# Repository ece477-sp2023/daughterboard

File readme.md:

# Things to change for v3

-   mosfet rotation
-   bulk capacitor on 2.5V plane
-   bulk capacitors directly on all regulator outputs
-   ftdi analog power from 5V
-   1.1V slow start from 3vi, not 3v3

# want to have

-   crystal for fpga?
-   crystal for ftdi?
    -   only if needed
-   indicator LEDs?
    -   power
    -   usb

# make sure before starting v3

-   ftdi chip works
    -   if not, have easy way to program flash

# notes for v3

-   8 layer board might give more space on top
-   don't need 1v1 slow start connected to both 3v3 and 2v5, just use 3v3
-   look at regulator stock for 5->3, don't know if footprint chosen is common / available

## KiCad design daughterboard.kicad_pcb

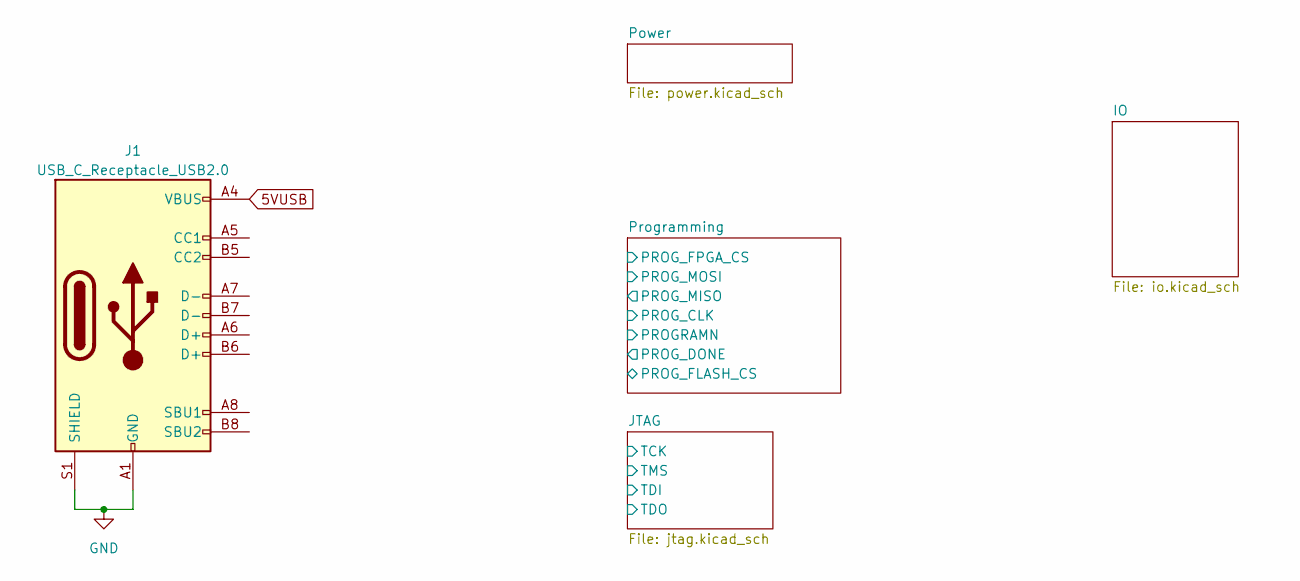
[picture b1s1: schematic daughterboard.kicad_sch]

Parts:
J1: USB_C_Receptacle_USB2.0; USB_C_GCT4105

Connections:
5VUSB: J1.A4 (VBUS), J1.A9 (VBUS), J1.B4 (VBUS), J1.B9 (VBUS); also elsewhere on the board
/JTAG/D+: J1.A6 (D+); also elsewhere on the board
/JTAG/D-: J1.A7 (D-); also elsewhere on the board
GND: J1.A1 (GND), J1.A12 (GND), J1.B1 (GND), J1.B12 (GND), J1.S1 (SHIELD); also elsewhere on the board

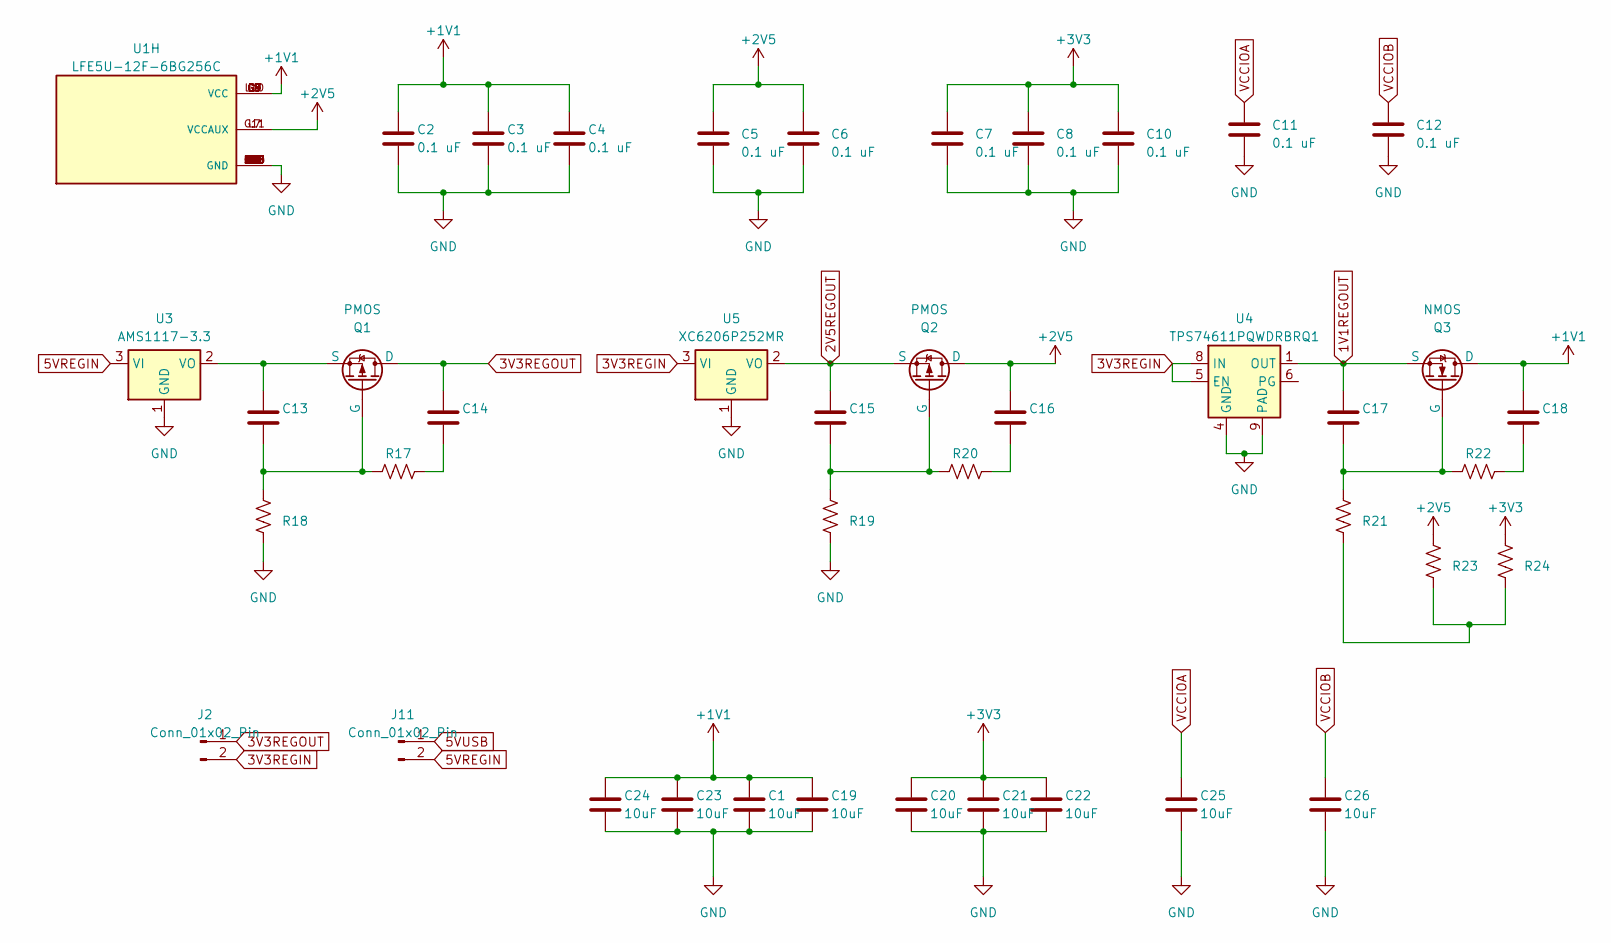
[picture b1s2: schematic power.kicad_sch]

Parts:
C1, C19, C20, C21, C22, C23, C24, C25, C26: 10uF; C_0805_2012Metric
C2, C3, C4, C5, C6, C7, C8, C10, C11, C12: 0.1 uF; C_0402_1005Metric
C13, C14, C15, C16, C17, C18: C_0805_2012Metric
J2, J11: Conn_01x02_Pin; PinHeader_1x02_P2.54mm_Vertical
Q1, Q2: PMOS; SOT-23-3
Q3: NMOS; SOT-23-3
R17, R18, R19, R20, R21, R22, R23, R24: R_0805_2012Metric
U1: LFE5U-12F-6BG256C; BGA256C80P16X16_1400X1400X170; PARTREV 2.0
U3: AMS1117-3.3; SOT-89-3
U4: TPS74611PQWDRBRQ1; Texas_S-PVSON-N8
U5: XC6206P252MR; SOT-23-3

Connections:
1V1REGOUT: C17.1, Q3.3 (S), U4.1 (OUT)
2V5REGOUT: C15.1, Q2.3 (S), U5.2 (VO)
3V3REGIN: J2.2, U4.5 (EN), U4.8 (IN), U5.3 (VI); also elsewhere on the board
3V3REGOUT: C14.1, J2.1, Q1.1 (D); also elsewhere on the board
5VREGIN: J11.2, U3.3 (VI); also elsewhere on the board
5VUSB: J11.1; also elsewhere on the board
+2V5: C5.1, C6.1, C16.1, Q2.1 (D), R23.2, U1.G11 (VCCAUX), U1.L7 (VCCAUX); also elsewhere on the board
GND: C1.2, C2.2, C3.2, C4.2, C5.2, C6.2, C7.2, C8.2, C10.2, C11.2, C12.2, C19.2, C20.2, C21.2, C22.2, C23.2, C24.2, C25.2, C26.2, R18.1, R19.1, U1.A1 (GND), U1.A16 (GND), U1.D2 (GND), U1.D15 (GND), U1.F8 (GND), U1.F9 (GND), U1.G8 (GND), U1.G10 (GND), U1.H1 (GND), U1.H8 (GND), U1.H9 (GND), U1.H10 (GND), U1.H16 (GND), U1.J8 (GND), U1.J9 (GND), U1.J10 (GND), U1.K6 (GND), U1.K7 (GND), U1.K8 (GND), U1.K9 (GND), U1.K10 (GND), U1.N2 (GND), U1.N15 (GND), U1.T1 (GND), U1.T5 (GND), U1.T12 (GND), U1.T16 (GND), U3.1 (GND), U4.4 (GND), U4.9 (PAD), U5.1 (GND); also elsewhere on the board
unnamed: C14.2, R17.1
unnamed: C16.2, R20.1
unnamed: C18.2, R22.1
unnamed: C13.2, Q1.2 (G), R17.2, R18.2
unnamed: C13.1, Q1.3 (S), U3.2 (VO)
unnamed: C15.2, Q2.2 (G), R19.2, R20.2
unnamed: C17.2, Q3.2 (G), R21.2, R22.2
unnamed: R21.1, R23.1, R24.1
VCCIOA: C11.1, C25.1; also elsewhere on the board
VCCIOB: C12.1, C26.1; also elsewhere on the board

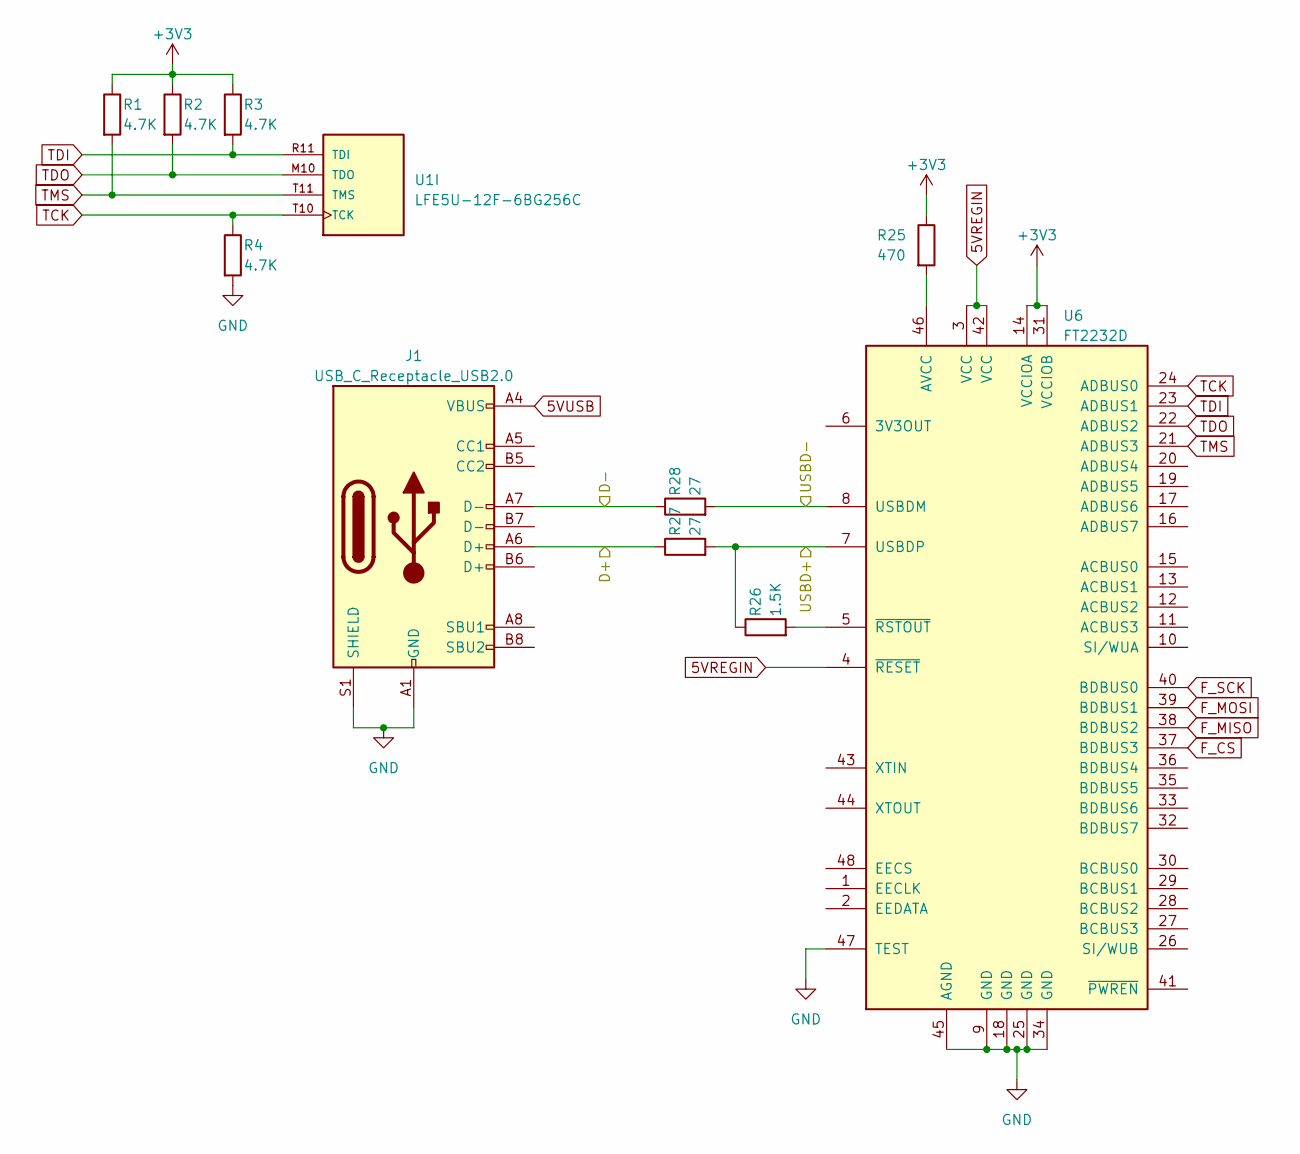
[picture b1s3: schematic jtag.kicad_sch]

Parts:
J1: USB_C_Receptacle_USB2.0; USB_C_GCT4105
R1, R2, R3, R4: 4.7K; R_0603_1608Metric
R25: 470; R_0603_1608Metric
R26: 1.5K; R_0603_1608Metric
R27, R28: 27; R_0603_1608Metric
U1: LFE5U-12F-6BG256C; BGA256C80P16X16_1400X1400X170; PARTREV 2.0
U6: FT2232D; LQFP-48_7x7mm_P0.5mm

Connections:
5VREGIN: U6.3 (VCC), U6.4 (~RESET), U6.42 (VCC); also elsewhere on the board
5VUSB: J1.A4 (VBUS), J1.A9 (VBUS), J1.B4 (VBUS), J1.B9 (VBUS); also elsewhere on the board
/JTAG/D+: J1.A6 (D+), R27.1
/JTAG/D-: J1.A7 (D-), R28.1
/JTAG/USBD+: R26.1, R27.2, U6.7 (USBDP)
/JTAG/USBD-: R28.2, U6.8 (USBDM)
F_CS: U6.37 (BDBUS3); also elsewhere on the board
F_MISO: U6.38 (BDBUS2); also elsewhere on the board
F_MOSI: U6.39 (BDBUS1); also elsewhere on the board
F_SCK: U6.40 (BDBUS0); also elsewhere on the board
GND: J1.A1 (GND), J1.A12 (GND), J1.B1 (GND), J1.B12 (GND), J1.S1 (SHIELD), R4.2, U6.9 (GND), U6.18 (GND), U6.25 (GND), U6.34 (GND), U6.45 (AGND), U6.47 (TEST); also elsewhere on the board
unnamed: R25.2, U6.46 (AVCC)
unnamed: R26.2, U6.5 (~RSTOUT)
TCK: R4.1, U1.T10 (TCK), U6.24 (ADBUS0); also elsewhere on the board
TDI: R3.2, U1.R11 (TDI), U6.23 (ADBUS1); also elsewhere on the board
TDO: R2.2, U1.M10 (TDO), U6.22 (ADBUS2); also elsewhere on the board
TMS: R1.2, U1.T11 (TMS), U6.21 (ADBUS3); also elsewhere on the board

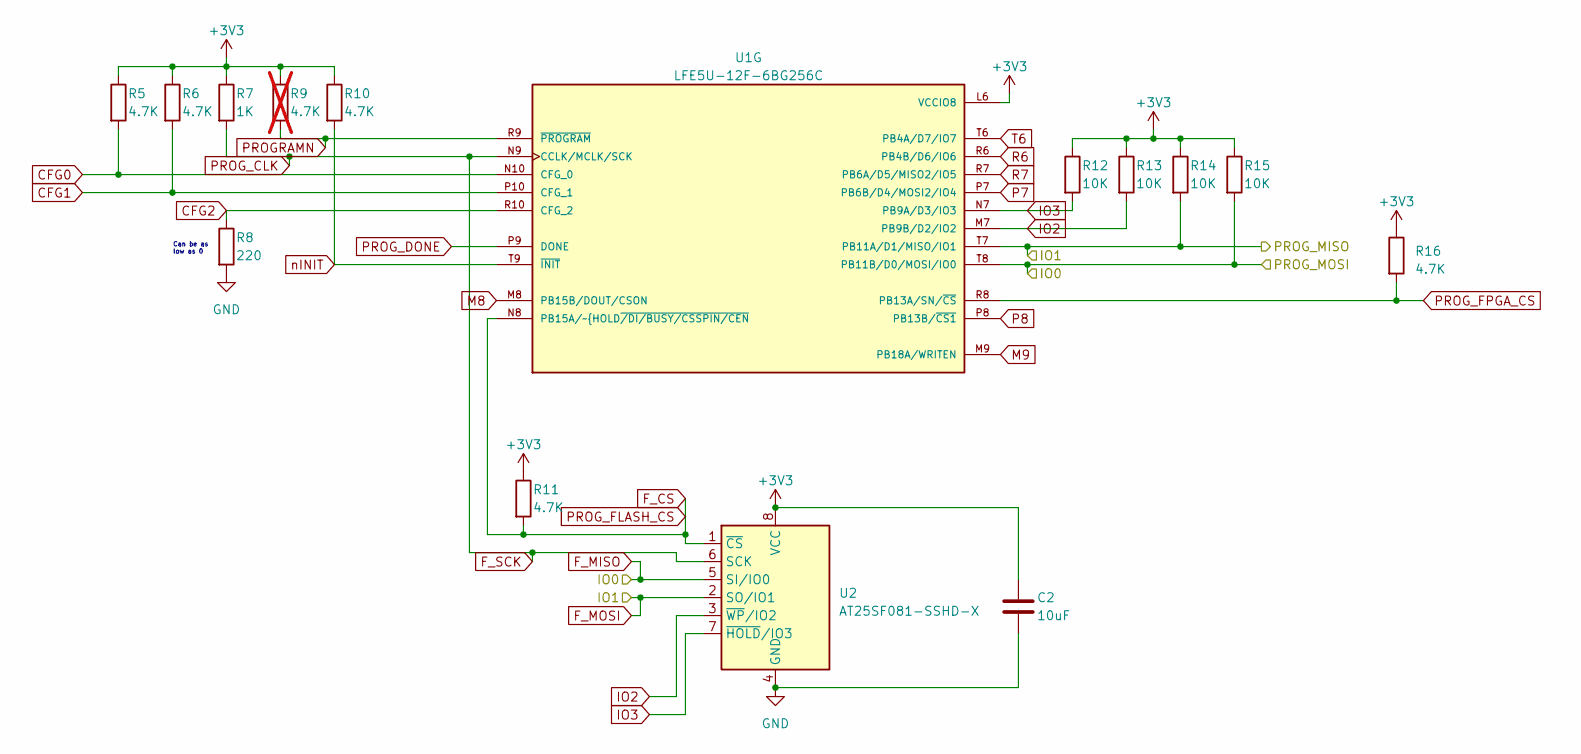
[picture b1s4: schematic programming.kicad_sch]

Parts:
C2: 10uF; C_0805_2012Metric
R5, R6, R10, R11, R16: 4.7K; R_0603_1608Metric
R7: 1K; R_0603_1608Metric
R8: 220; R_0603_1608Metric
R9: 4.7K; R_0603_1608Metric; not fitted
R12, R13, R14, R15: 10K; R_0603_1608Metric
U1: LFE5U-12F-6BG256C; BGA256C80P16X16_1400X1400X170; PARTREV 2.0
U2: AT25SF081-SSHD-X; SOIC-8_3.9x4.9mm_P1.27mm

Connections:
CFG0: R5.2, U1.N10 (CFG_0); also elsewhere on the board
CFG1: R6.2, U1.P10 (CFG_1); also elsewhere on the board
CFG2: R8.1, U1.R10 (CFG_2); also elsewhere on the board
F_CS: R11.2, U1.N8 (PB15A/~HOLD~{/DI/BUSY/CSSPIN/CEN), U2.1 (~CS); also elsewhere on the board
F_MISO: R15.2, U1.T8 (PB11B/D0/MOSI/IO0), U2.5 (SI/IO0); also elsewhere on the board
F_MOSI: R14.2, U1.T7 (PB11A/D1/MISO/IO1), U2.2 (SO/IO1); also elsewhere on the board
F_SCK: R7.2, U1.N9 (CCLK/MCLK/SCK), U2.6 (SCK); also elsewhere on the board
GND: C2.2, R8.2, U2.4 (GND); also elsewhere on the board
IO2: R13.2, U1.M7 (PB9B/D2/IO2), U2.3 (~WP/IO2); also elsewhere on the board
IO3: R12.2, U1.N7 (PB9A/D3/IO3), U2.7 (~HOLD/IO3); also elsewhere on the board
M8: U1.M8 (PB15B/DOUT/CSON); also elsewhere on the board
M9: U1.M9 (PB18A/WRITEN); also elsewhere on the board
P7: U1.P7 (PB6B/D4/MOSI2/IO4); also elsewhere on the board
P8: U1.P8 (PB13B/~CS1); also elsewhere on the board
PROGRAMN: R9.2, U1.R9 (~PROGRAM); also elsewhere on the board
PROG_DONE: U1.P9 (DONE); also elsewhere on the board
PROG_FPGA_CS: R16.2, U1.R8 (PB13A/SN/~CS); also elsewhere on the board
R6: U1.R6 (PB4B/D6/IO6); also elsewhere on the board
R7: U1.R7 (PB6A/D5/MISO2/IO5); also elsewhere on the board
T6: U1.T6 (PB4A/D7/IO7); also elsewhere on the board
nINIT: R10.2, U1.T9 (~INIT); also elsewhere on the board

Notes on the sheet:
Can be as low as 0

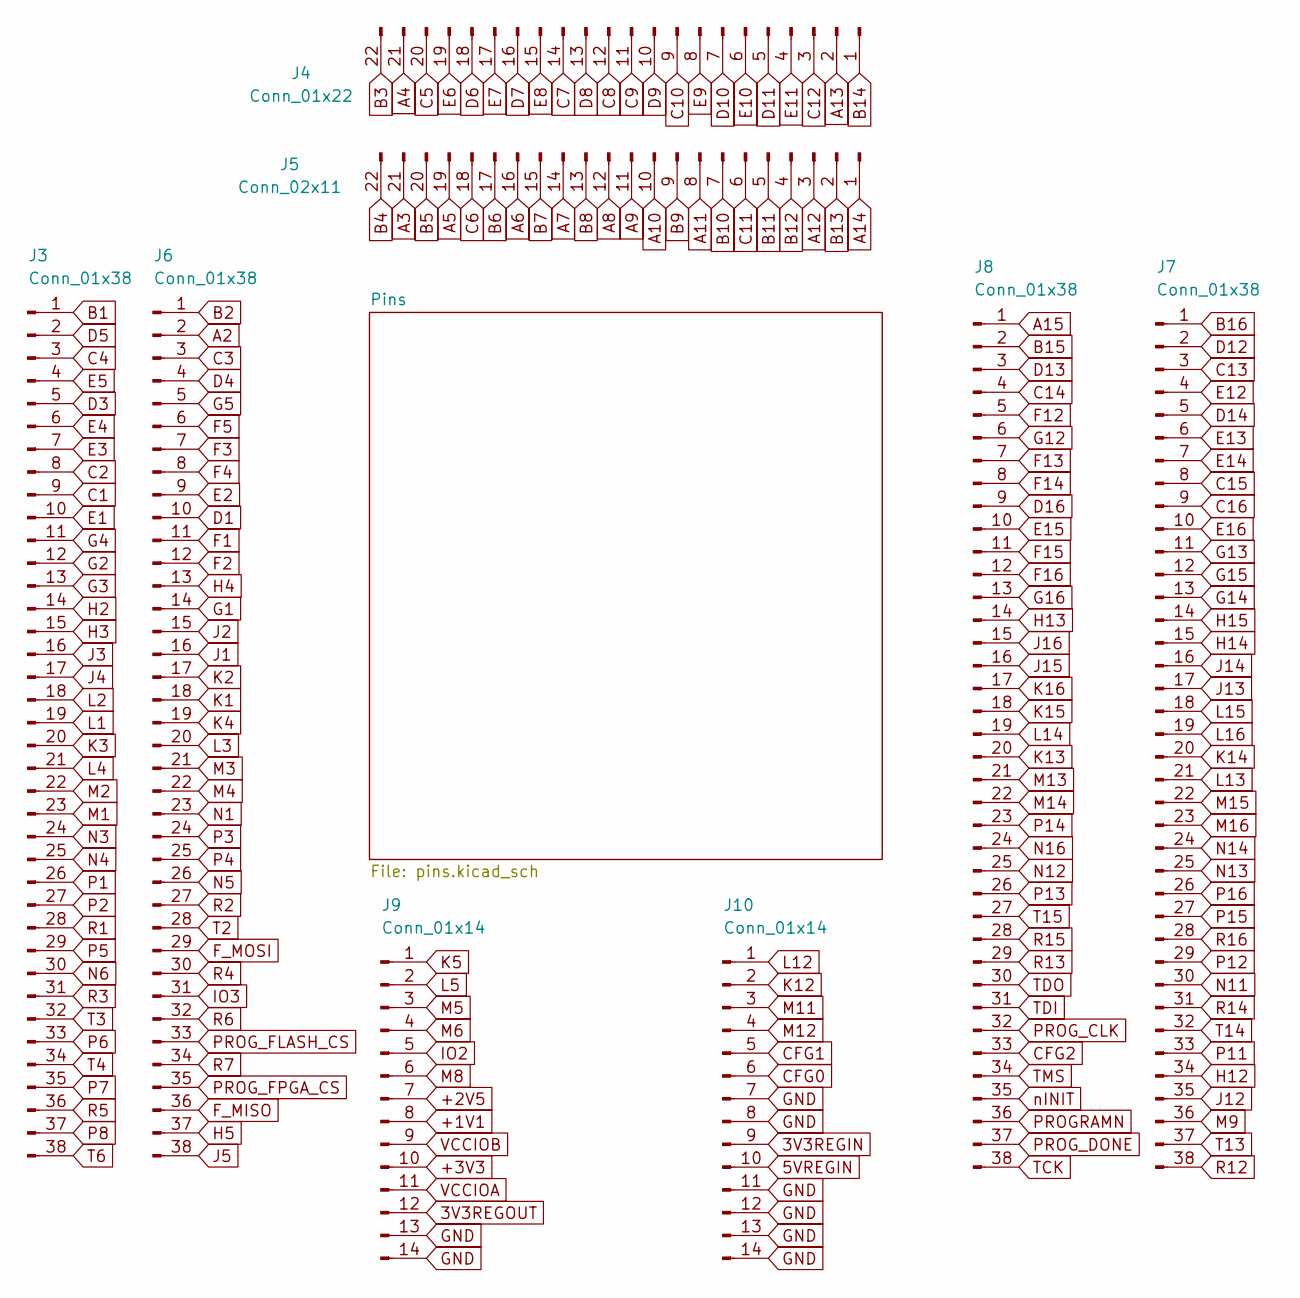
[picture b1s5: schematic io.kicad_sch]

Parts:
J3, J7: Conn_01x38; PinHeader_1x38_P1.27mm_Vertical
J4: Conn_01x22; PinHeader_1x22_P1.27mm_Vertical
J5: Conn_02x11; PinHeader_2x11_P2.54mm_Vertical
J6, J8: Conn_01x38; PinHeader_2x19_P2.54mm_Vertical
J9, J10: Conn_01x14; PinHeader_2x07_P2.54mm_Vertical

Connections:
3V3REGIN: J10.9; also elsewhere on the board
3V3REGOUT: J9.12; also elsewhere on the board
5VREGIN: J10.10; also elsewhere on the board
+2V5: J9.7; also elsewhere on the board
A2: J6.2; also elsewhere on the board
A3: J5.21; also elsewhere on the board
A4: J4.21; also elsewhere on the board
A5: J5.19; also elsewhere on the board
A6: J5.16; also elsewhere on the board
A7: J5.14; also elsewhere on the board
A8: J5.12; also elsewhere on the board
A9: J5.11; also elsewhere on the board
A10: J5.10; also elsewhere on the board
A11: J5.8; also elsewhere on the board
A12: J5.3; also elsewhere on the board
A13: J4.2; also elsewhere on the board
A14: J5.1; also elsewhere on the board
A15: J8.1; also elsewhere on the board
B1: J3.1; also elsewhere on the board
B2: J6.1; also elsewhere on the board
B3: J4.22; also elsewhere on the board
B4: J5.22; also elsewhere on the board
B5: J5.20; also elsewhere on the board
B6: J5.17; also elsewhere on the board
B7: J5.15; also elsewhere on the board
B8: J5.13; also elsewhere on the board
B9: J5.9; also elsewhere on the board
B10: J5.7; also elsewhere on the board
B11: J5.5; also elsewhere on the board
B12: J5.4; also elsewhere on the board
B13: J5.2; also elsewhere on the board
B14: J4.1; also elsewhere on the board
B15: J8.2; also elsewhere on the board
B16: J7.1; also elsewhere on the board
C1: J3.9; also elsewhere on the board
C2: J3.8; also elsewhere on the board
C3: J6.3; also elsewhere on the board
C4: J3.3; also elsewhere on the board
C5: J4.20; also elsewhere on the board
C6: J5.18; also elsewhere on the board
C7: J4.14; also elsewhere on the board
C8: J4.12; also elsewhere on the board
C9: J4.11; also elsewhere on the board
C10: J4.9; also elsewhere on the board
C11: J5.6; also elsewhere on the board
C12: J4.3; also elsewhere on the board
C13: J7.3; also elsewhere on the board
C14: J8.4; also elsewhere on the board
C15: J7.8; also elsewhere on the board
C16: J7.9; also elsewhere on the board
CFG0: J10.6; also elsewhere on the board
CFG1: J10.5; also elsewhere on the board
CFG2: J8.33; also elsewhere on the board
D1: J6.10; also elsewhere on the board
D3: J3.5; also elsewhere on the board
D4: J6.4; also elsewhere on the board
D5: J3.2; also elsewhere on the board
D6: J4.18; also elsewhere on the board
D7: J4.16; also elsewhere on the board
D8: J4.13; also elsewhere on the board
D9: J4.10; also elsewhere on the board
D10: J4.7; also elsewhere on the board
D11: J4.5; also elsewhere on the board
D12: J7.2; also elsewhere on the board
D13: J8.3; also elsewhere on the board
D14: J7.5; also elsewhere on the board
D16: J8.9; also elsewhere on the board
E1: J3.10; also elsewhere on the board
E2: J6.9; also elsewhere on the board
E3: J3.7; also elsewhere on the board
E4: J3.6; also elsewhere on the board
E5: J3.4; also elsewhere on the board
E6: J4.19; also elsewhere on the board
E7: J4.17; also elsewhere on the board
E8: J4.15; also elsewhere on the board
E9: J4.8; also elsewhere on the board
E10: J4.6; also elsewhere on the board
E11: J4.4; also elsewhere on the board
E12: J7.4; also elsewhere on the board
E13: J7.6; also elsewhere on the board
E14: J7.7; also elsewhere on the board
E15: J8.10; also elsewhere on the board
E16: J7.10; also elsewhere on the board
F1: J6.11; also elsewhere on the board
F2: J6.12; also elsewhere on the board
F3: J6.7; also elsewhere on the board
F4: J6.8; also elsewhere on the board
F5: J6.6; also elsewhere on the board
F12: J8.5; also elsewhere on the board
F13: J8.7; also elsewhere on the board
F14: J8.8; also elsewhere on the board
F15: J8.11; also elsewhere on the board
F16: J8.12; also elsewhere on the board
F_CS: J6.33; also elsewhere on the board
F_MISO: J6.36; also elsewhere on the board
F_MOSI: J6.29; also elsewhere on the board
F_SCK: J8.32; also elsewhere on the board
G1: J6.14; also elsewhere on the board
G2: J3.12; also elsewhere on the board
G3: J3.13; also elsewhere on the board
G4: J3.11; also elsewhere on the board
G5: J6.5; also elsewhere on the board
G12: J8.6; also elsewhere on the board
G13: J7.11; also elsewhere on the board
G14: J7.13; also elsewhere on the board
G15: J7.12; also elsewhere on the board
G16: J8.13; also elsewhere on the board
GND: J9.13, J9.14, J10.7, J10.8, J10.11, J10.12, J10.13, J10.14; also elsewhere on the board
H2: J3.14; also elsewhere on the board
H3: J3.15; also elsewhere on the board
H4: J6.13; also elsewhere on the board
H5: J6.37; also elsewhere on the board
H12: J7.34; also elsewhere on the board
H13: J8.14; also elsewhere on the board
H14: J7.15; also elsewhere on the board
H15: J7.14; also elsewhere on the board
IO2: J9.5; also elsewhere on the board
IO3: J6.31; also elsewhere on the board
J1: J6.16; also elsewhere on the board
J2: J6.15; also elsewhere on the board
J3: J3.16; also elsewhere on the board
J4: J3.17; also elsewhere on the board
J5: J6.38; also elsewhere on the board
J12: J7.35; also elsewhere on the board
J13: J7.17; also elsewhere on the board
J14: J7.16; also elsewhere on the board
J15: J8.16; also elsewhere on the board
J16: J8.15; also elsewhere on the board
K1: J6.18; also elsewhere on the board
K2: J6.17; also elsewhere on the board
K3: J3.20; also elsewhere on the board
K4: J6.19; also elsewhere on the board
K5: J9.1; also elsewhere on the board
K12: J10.2; also elsewhere on the board
K13: J8.20; also elsewhere on the board
K14: J7.20; also elsewhere on the board
K15: J8.18; also elsewhere on the board
K16: J8.17; also elsewhere on the board
L1: J3.19; also elsewhere on the board
L2: J3.18; also elsewhere on the board
L3: J6.20; also elsewhere on the board
L4: J3.21; also elsewhere on the board
L5: J9.2; also elsewhere on the board
L12: J10.1; also elsewhere on the board
L13: J7.21; also elsewhere on the board
L14: J8.19; also elsewhere on the board
L15: J7.18; also elsewhere on the board
L16: J7.19; also elsewhere on the board
M1: J3.23; also elsewhere on the board
M2: J3.22; also elsewhere on the board
M3: J6.21; also elsewhere on the board
M4: J6.22; also elsewhere on the board
M5: J9.3; also elsewhere on the board
M6: J9.4; also elsewhere on the board
M8: J9.6; also elsewhere on the board
M9: J7.36; also elsewhere on the board
M11: J10.3; also elsewhere on the board
M12: J10.4; also elsewhere on the board
M13: J8.21; also elsewhere on the board
M14: J8.22; also elsewhere on the board
M15: J7.22; also elsewhere on the board
M16: J7.23; also elsewhere on the board
N1: J6.23; also elsewhere on the board
N3: J3.24; also elsewhere on the board
N4: J3.25; also elsewhere on the board
N5: J6.26; also elsewhere on the board
N6: J3.30; also elsewhere on the board
N11: J7.30; also elsewhere on the board
N12: J8.25; also elsewhere on the board
N13: J7.25; also elsewhere on the board
N14: J7.24; also elsewhere on the board
N16: J8.24; also elsewhere on the board
P1: J3.26; also elsewhere on the board
P2: J3.27; also elsewhere on the board
P3: J6.24; also elsewhere on the board
P4: J6.25; also elsewhere on the board
P5: J3.29; also elsewhere on the board
P6: J3.33; also elsewhere on the board
P7: J3.35; also elsewhere on the board
P8: J3.37; also elsewhere on the board
P11: J7.33; also elsewhere on the board
P12: J7.29; also elsewhere on the board
P13: J8.26; also elsewhere on the board
P14: J8.23; also elsewhere on the board
P15: J7.27; also elsewhere on the board
P16: J7.26; also elsewhere on the board
PROGRAMN: J8.36; also elsewhere on the board
PROG_DONE: J8.37; also elsewhere on the board
PROG_FPGA_CS: J6.35; also elsewhere on the board
R1: J3.28; also elsewhere on the board
R2: J6.27; also elsewhere on the board
R3: J3.31; also elsewhere on the board
R4: J6.30; also elsewhere on the board
R5: J3.36; also elsewhere on the board
R6: J6.32; also elsewhere on the board
R7: J6.34; also elsewhere on the board
R12: J7.38; also elsewhere on the board
R13: J8.29; also elsewhere on the board
R14: J7.31; also elsewhere on the board
R15: J8.28; also elsewhere on the board
R16: J7.28; also elsewhere on the board
T2: J6.28; also elsewhere on the board
T3: J3.32; also elsewhere on the board
T4: J3.34; also elsewhere on the board
T6: J3.38; also elsewhere on the board
T13: J7.37; also elsewhere on the board
T14: J7.32; also elsewhere on the board
T15: J8.27; also elsewhere on the board
TCK: J8.38; also elsewhere on the board
TDI: J8.31; also elsewhere on the board
TDO: J8.30; also elsewhere on the board
TMS: J8.34; also elsewhere on the board
VCCIOA: J9.11; also elsewhere on the board
VCCIOB: J9.9; also elsewhere on the board
nINIT: J8.35; also elsewhere on the board
